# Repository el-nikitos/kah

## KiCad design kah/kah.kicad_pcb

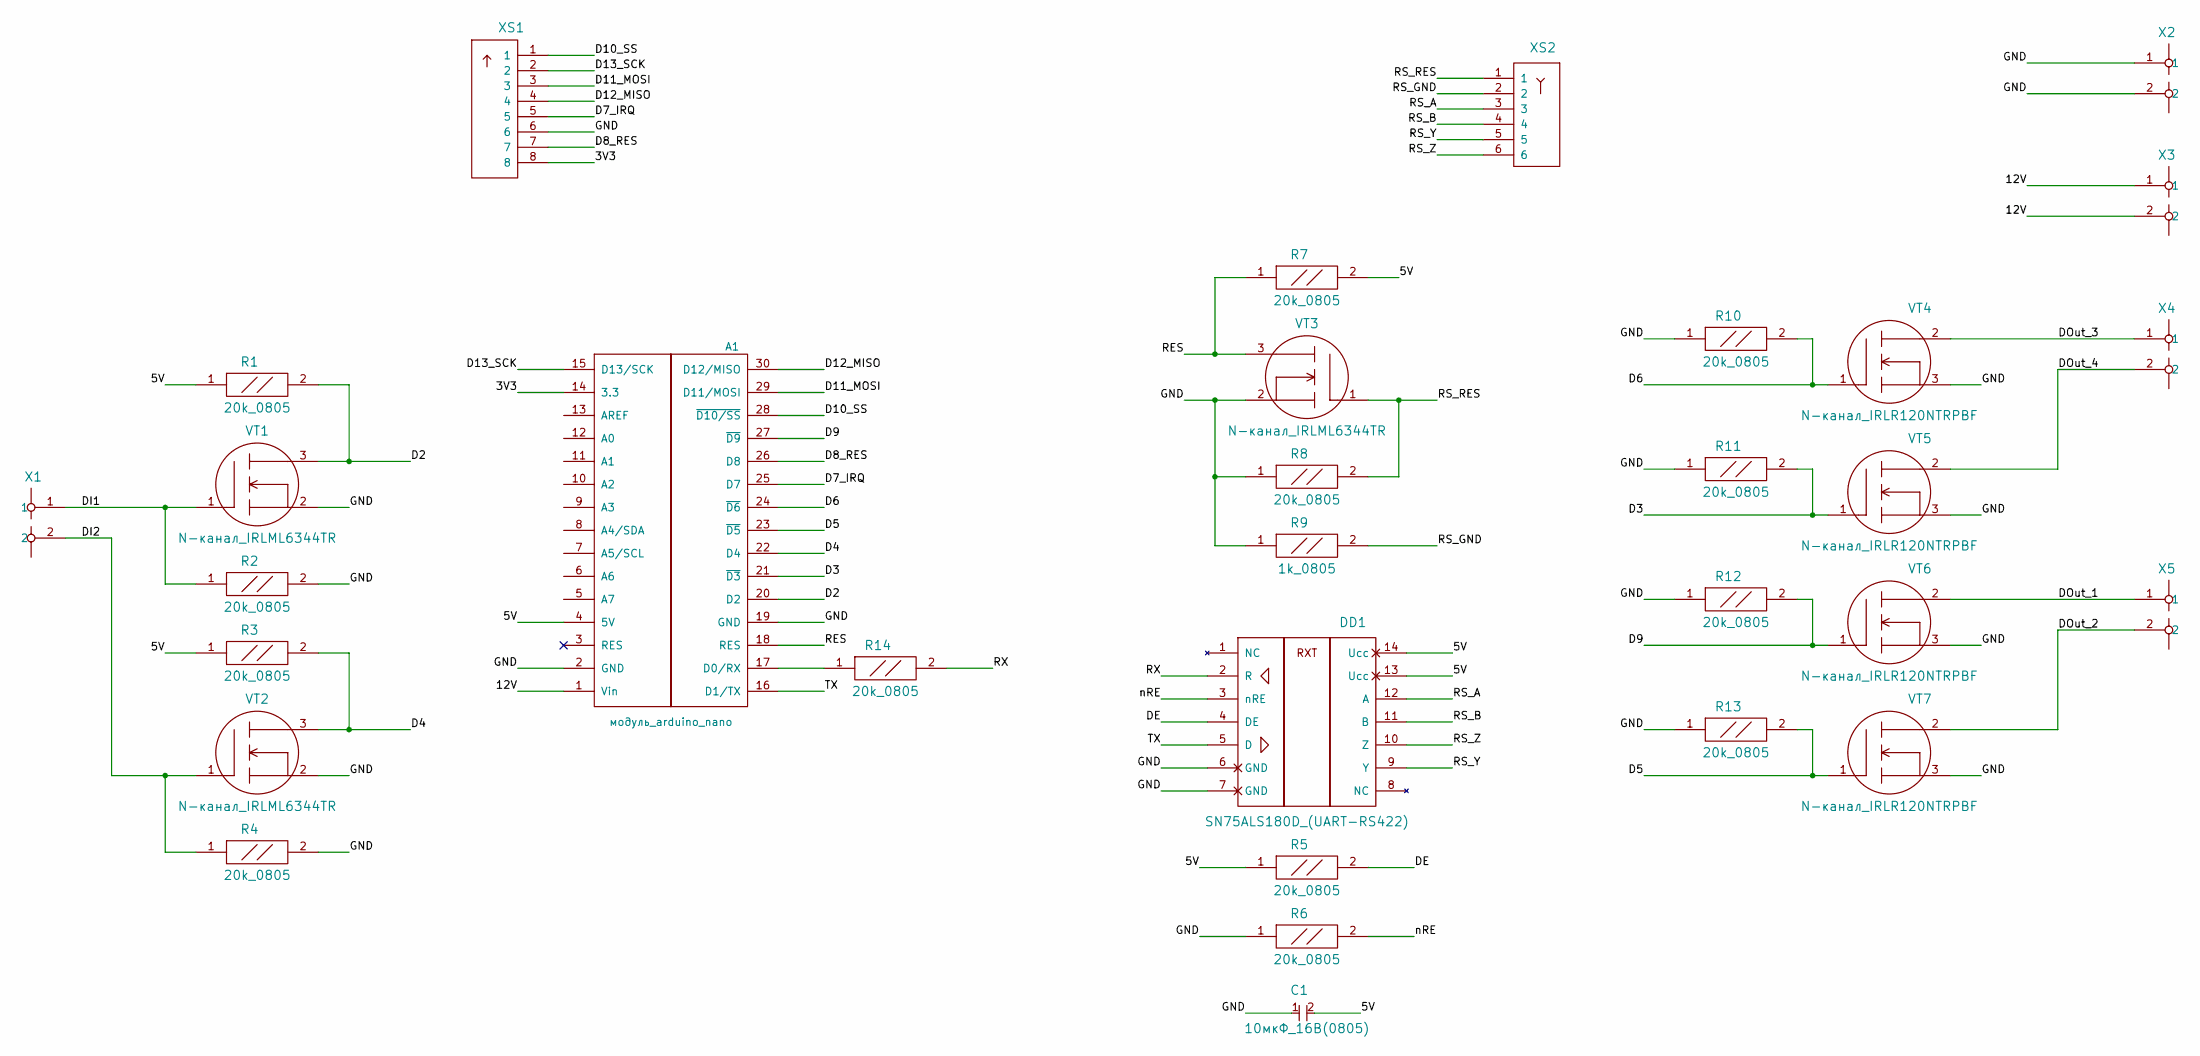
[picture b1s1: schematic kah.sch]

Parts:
A1: модуль_arduino_nano; Arduino_nano
C1: 10мкФ_16В(0805); Конденсатор_SMD_0805
DD1: SN75ALS180D_(UART-RS422); SO-14
R1, R2, R3, R4, R5, R6, R7, R8, R10, R11, R12, R13, R14: 20k_0805; Резистор_SMD_0805_0,125Вт
R9: 1k_0805; Резистор_SMD_0805_0,125Вт
VT1, VT2, VT3: N-канал_IRLML6344TR; Транзистор_IRLML6344TR_SOT-23
VT4, VT5, VT6, VT7: N-канал_IRLR120NTRPBF; Транзистор_N-канал_dpak
X1, X2, X3, X4, X5: Клеммник_х2; Клеммник_х2_шаг5
XS1: Вилка_PLS8; Вилка_PLS8_вертикальная
XS2: Розетка_PBS6; Розетка_RJ11_6P6C

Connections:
/3V3: A1.14 (3.3), XS1.8
/5V: A1.4 (5V), C1.2, DD1.13 (Ucc), DD1.14 (Ucc), R1.1, R3.1, R5.1, R7.2
/12V: A1.1 (Vin), X3.1, X3.2
/D2: A1.20 (D2), R1.2, VT1.3
/D3: A1.21 (~D3), R11.2, VT5.1
/D4: A1.22 (D4), R3.2, VT2.3
/D5: A1.23 (~D5), R13.2, VT7.1
/D6: A1.24 (~D6), R10.2, VT4.1
/D7_IRQ: A1.25 (D7), XS1.5
/D8_RES: A1.26 (D8), XS1.7
/D9: A1.27 (~D9), R12.2, VT6.1
/D10_SS: A1.28 (~D10/SS), XS1.1
/D11_MOSI: A1.29 (D11/MOSI), XS1.3
/D12_MISO: A1.30 (D12/MISO), XS1.4
/D13_SCK: A1.15 (D13/SCK), XS1.2
/DE: DD1.4 (DE), R5.2
/DI1: R2.1, VT1.1, X1.1
/DI2: R4.1, VT2.1, X1.2
/DOut_1: VT6.2, X5.1
/DOut_2: VT7.2, X5.2
/DOut_3: VT4.2, X4.1
/DOut_4: VT5.2, X4.2
/GND: A1.2 (GND), A1.19 (GND), C1.1, DD1.6 (GND), DD1.7 (GND), R2.2, R4.2, R6.1, R8.1, R9.1, R10.1, R11.1, R12.1, R13.1, VT1.2, VT2.2, VT3.2, VT4.3, VT5.3, VT6.3, VT7.3, X2.1, X2.2, XS1.6
/RES: A1.18 (RES), R7.1, VT3.3
/RS_A: DD1.12 (A), XS2.3
/RS_B: DD1.11 (B), XS2.4
/RS_GND: R9.2, XS2.2
/RS_RES: R8.2, VT3.1, XS2.1
/RS_Y: DD1.9 (Y), XS2.5
/RS_Z: DD1.10 (Z), XS2.6
/RX: DD1.2 (R), R14.2
/TX: A1.16 (D1/TX), DD1.5 (D)
/nRE: DD1.3 (nRE), R6.2
unnamed: A1.17 (D0/RX), R14.1

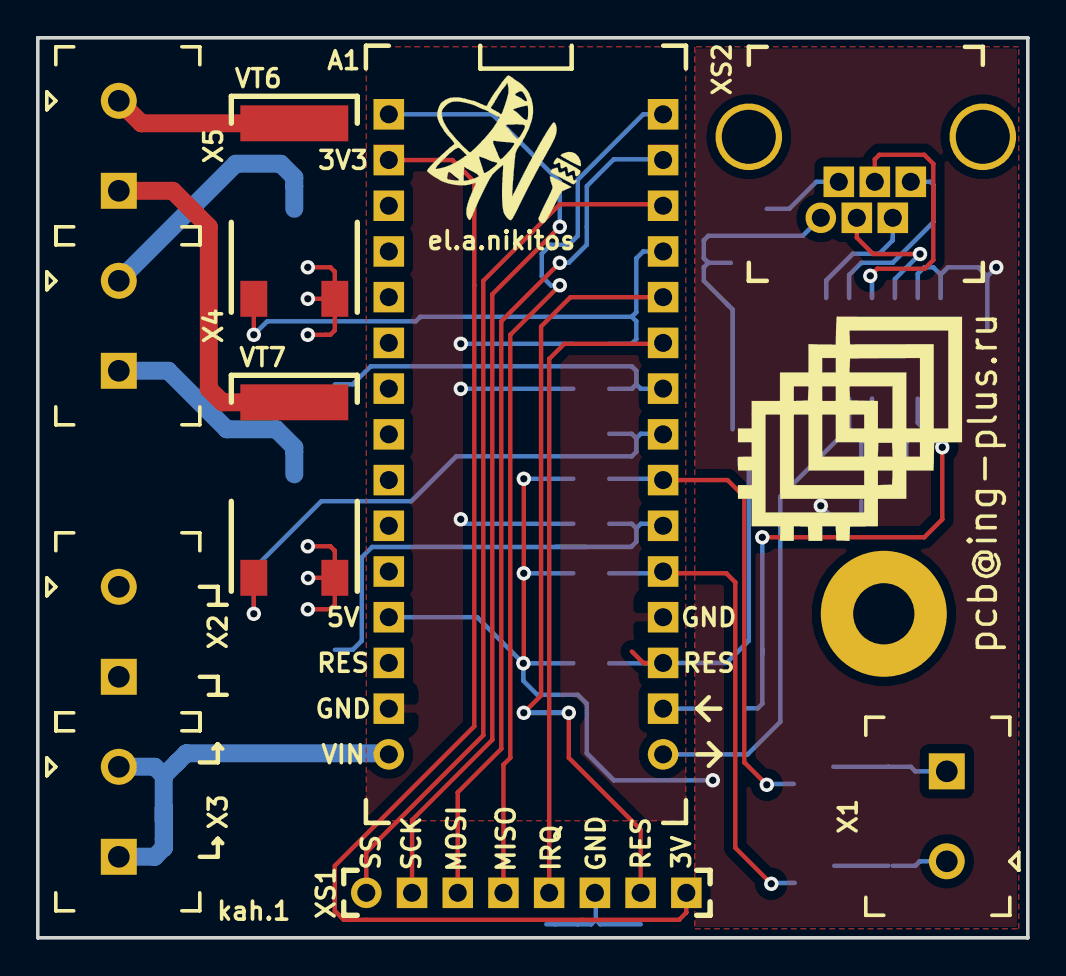
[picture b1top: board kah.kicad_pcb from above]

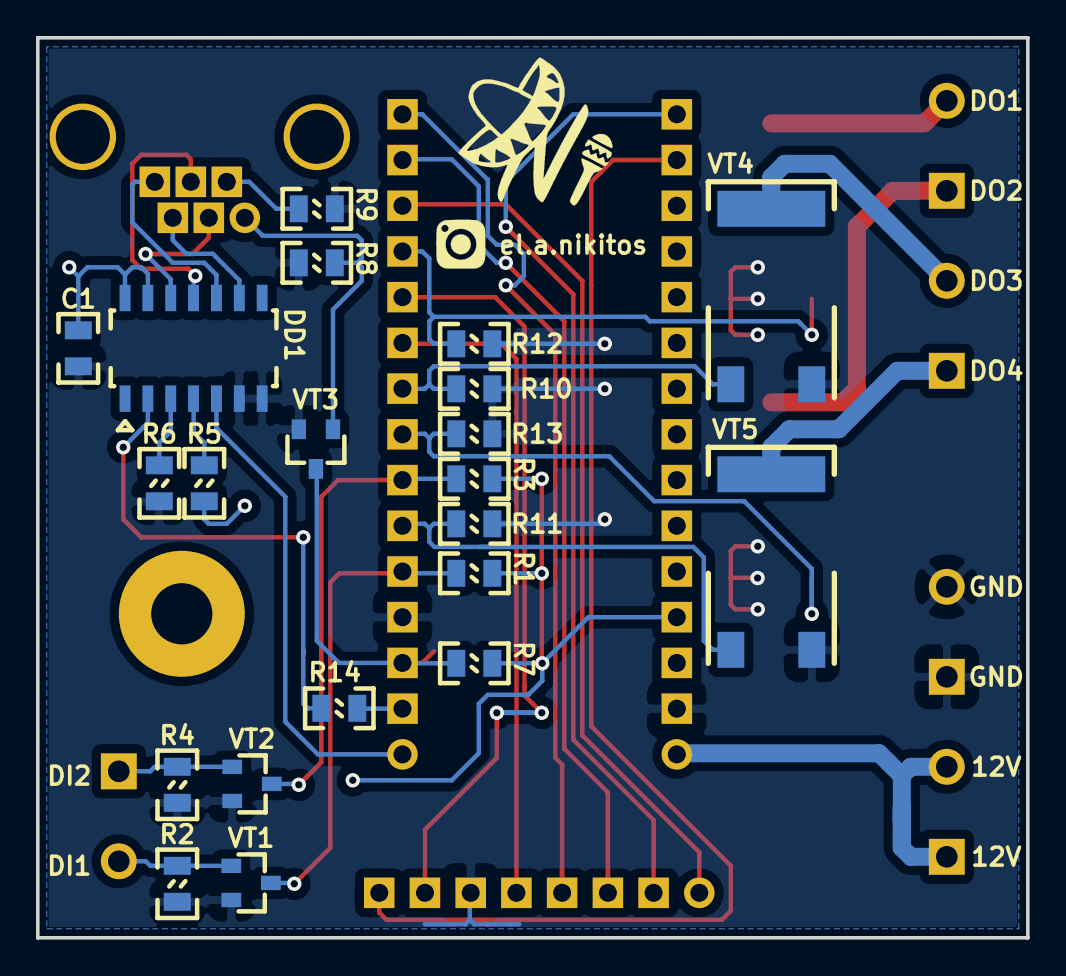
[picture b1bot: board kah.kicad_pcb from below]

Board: 2 copper layers, 55.0 x 50.0 mm, 32 parts (21 on the bottom side), 34 nets.

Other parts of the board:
M3: Отверстие_М3

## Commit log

2019-07-23 есть схема без входов и подключения rfid
2019-07-24 начата трассировка
2019-07-28 готова трассировка (50х55 мм)
2019-08-06 добавлено согласующее сопротивление на RX - изменена версия
2019-08-11 переливающийся скетч и библиотека для rfid
